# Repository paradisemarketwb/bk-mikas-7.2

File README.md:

# БК Микас7.2 · HUNTER R2

> **Hunter Reference preview:** ветка `feat/hunter-reference-ui`,
> [PR №3](https://github.com/paradisemarketwb/bk-mikas-7.2/pull/3).
> Classic R2 сохранён; новый стиль, жесты, конструктор и калибровки описаны
> в [статусе Hunter](docs/lvgl/HUNTER_STATUS.md). В main до приёмки не сливается.

Круглый сенсорный бортовой компьютер для УАЗ Hunter / ЗМЗ-409 / Микас7.2:
Waveshare ESP32-S3-Touch-LCD-2.1,480×480, проводная K-Line через L9637D.
Работает без интернета; телефон подключается к локальной сети прибора.

Это действующая переработанная версия проекта. Старые R0/R1/R1B, инструкции,
рисунки и браузерное демо находятся только в [archive/r1b](archive/README.md).

**Разработаны** собственные схемы и PCB интерфейса и питания, Gerber/Excellon/BOM,
корпуса CAD/STL, прошивка ESP-IDF, декларативный LVGL-интерфейс, native simulator,
конструктор с телефона, NVS-профили, журналы и OTA. **Физические испытания не
проводились**: перед установкой нужны квалификация питания/импульсов, проверка
ROM/BOOT/UART, нагрева, дисплея/сенсора и посадки конкретного экземпляра.
[Точный статус по ТЗ и результаты проверок](docs/R2_STATUS.md).

## С чего начать

1. [Пошаговое начало работы](docs/GETTING_STARTED.md).
2. [Компоненты и покупка](docs/BOM.md), [заказ PCB](docs/assembly/PCB_ORDER.md).
3. [Сборка, пайка, мультиметр и стенд](docs/assembly/ASSEMBLY.md).
4. [Полная проводка и распиновка](docs/WIRING.md).
5. [Windows10: сборка и прошивка](docs/firmware/R2.md).
6. [Телефон: конструктор, JSON и OTA](docs/getting-started/PHONE.md).
7. [LVGL Simulator для Windows/Linux](simulator/README.md).
8. [Диагностика неисправностей](docs/troubleshooting/DIAGNOSTICS.md).

## Два варианта подключения

- **R2 UART/L9637D** — собственные интерфейсная и силовая платы.
- **USB-KKL / FT232RL** — дополнительная отдельная прошивка, существующий KKL,
  готовый USB-A разъём, два22Ω и внешнее5V питание. Компьютер в работе не нужен.
  [Готовая прошивка с инструкциями](downloads/README.md),
  [подключение](docs/wiring/USB_KKL.md) и [сборка/прошивка](docs/firmware/USB_KKL.md).

Режимы взаимоисключающие: GPIO19 используется либо как TX_ARM, либо как D−.
На оригинальном дисплее два USB-C, ручного USB-select нет; UART выбирается
автоматически. Для работы UART питание подаётся на J9.2, UART-портJ2 должен
быть отключён от ПК. Точные исправленные инструкции — в документации проводки.

[Как менять экраны: JSON/телефон или C-код](docs/lvgl/SCREEN_CUSTOMIZATION.md).

## Платы и корпуса

Готовые архивы: [Gerber/сверловка/BOM двух плат](hardware/fabrication/BK-R2-prototype-fabrication.zip) · [STL и исходники корпусов](hardware/fabrication/BK-R2-printable-cases.zip).

- [BK-KLINE-R2](hardware/kicad/r2/README.md): L9637D, уровни3V3,
  аппаратный TX_ARM, сервисное отключение, внешний clamp K-Line.
  [KiCad](hardware/kicad/r2/BK-KLINE-R2.kicad_pro),
  [Gerber/сверловка](hardware/kicad/r2/fabrication-prototype/),
  [BOM](hardware/kicad/r2/BOM.csv), [CAD-экспорты](hardware/kicad/r2/exports/).
- [BK-POWER-R2](hardware/kicad/power-r2/README.md): автомобильный вход,
  reverse/OV/UV, MOSFET/TVS, RECOM5V и ideal-diode ORing USB.
  [KiCad](hardware/kicad/power-r2/BK-POWER-R2.kicad_pro).
- [Корпуса R2, исходники, размеры и STL](hardware/case/r2/README.md).

Номера наших JST не повторяют12PIN Waveshare. GPIO0 исключён; GPIO19 занят
TX_ARM, nativeUSB запрещён в UART-режимеR2. Рабочее питание — J9.2 USB_5V; обаType-C пустые. Для прошивки снятьJP1 и временно подключитьПК к отдельному UART Type-C J2/CH343. РучногоUSB-select нет; наличиеVBUS наJ2 автоматически отключает внешнийUART43/44. После прошивки снятькабель. Прямые12В на дисплей запрещены. Дополнительный режим [USB-KKL без R2-плат](docs/wiring/USB_KKL.md) используетGPIO19/20 какUSB; R2-жгут при этом отключается.
Файлы производства получены из реальных PCB, но программные ERC/DRC не являются
испытанием load dump или серийной автомобильной квалификацией.

## Прошивка и интерфейс

ESP-IDF5.5.1 + LVGL9.6.0. Собственный monitor0B,9600,8N1 из
[uaz-mikas-diagnostics](https://github.com/paradisemarketwb/uaz-mikas-diagnostics).
Реализованы framing/checksum/escaping/echo, reconnect и чтение11метрик/DTC.
Команд записи EEPROM, управления форсунками/вентилятором и стирания ошибок нет.

До8приборов по8виджетов: числа, подписи, дуги, стрелка, уровень, температура,
статус, предупреждение и мини-график. JSON задаёт положение/размер, метрику,
диапазон/пороги, цвет/фон, единицы, точность и видимость. Добавление экрана
не требует менять протокол ЭБУ. Есть10базовых видов, темы, свайпы, сенсорный
редактор, яркостьPWM, векторная заставкаHunter и подробные ошибки.
[Общий код и API](docs/lvgl/IMPLEMENTATION.md).

Телефон: WPA2 с уникальным паролем + отдельная HTTP-авторизация, просмотр
данных/ошибок/истории, конструктор, порядок/тема/яркость, JSON import/export,
заводской профиль и OTA в неактивный раздел с проверкой SHA256/ESP-образа.
[Исходник страницы](firmware/components/wifi/index.html),
[вид на телефоне](docs/images/web/phone-editor.png).

Скорость, пробег, остаток топлива и запас хода без датчиков не выдумываются.
ДМРВ ждёт подтверждения коэффициента, лямбда отображается raw. Данные
скриншотов и симулятора искусственные. Референс-изображения десяти экранов
в текущих вложениях нет, соответствие ему не заявляется.

## Проверки и документация

- [Архитектура](docs/ARCHITECTURE.md) и [протокол/формулы](docs/PROTOCOL.md).
- [Команды проверок и отчёты](docs/TESTING.md).
- [Сверка всех пунктов ТЗ](docs/requirements/MATRIX.md), [исходное ТЗ](docs/requirements/SPEC.md).
- [GitHub PR](https://github.com/paradisemarketwb/bk-mikas-7.2/pull/1).

Публичный репозиторий не содержит персональных диагностических логов, VIN,
паролей владельца и ключей. Уникальные credentials генерируются только на устройстве.

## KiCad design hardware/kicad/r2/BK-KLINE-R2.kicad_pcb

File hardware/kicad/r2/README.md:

# BK-KLINE-R2 — интерфейс Микас7.2

Настоящая схема и двухслойная PCB65×52mm,49 подключённых площадок. GPIO0 исключён, предусмотрены L9637D, аппаратный буферTX,22Ω pulse-proof ветвь и SMAJ18A clamp. ERC/DRC/netlist проверены программно. **Стендовых и автомобильных испытаний не было.**

- [Схема](BK-KLINE-R2.kicad_sch), [PCB](BK-KLINE-R2.kicad_pcb), [проект](BK-KLINE-R2.kicad_pro), [BOM](BOM.csv), [соединения](NETLIST.csv).
- [PDF схемы](exports/BK-KLINE-R2.pdf), [SVG схемы](exports/BK-KLINE-R2.svg), [верх](exports/pcb-top.svg), [низ](exports/pcb-bottom.svg), [3D](exports/pcb-3d.png), [STEP](exports/BK-KLINE-R2.step).
- [Gerber/позиции/PTH/NPTH](fabrication-prototype/), [ERC](reports/ERC.txt), [DRC](reports/DRC.txt), [SHA256](reports/SHA256.json).

## Подключение

|Разъём|Назначение|
|---|---|
|J1.1|VS_PROT от защищённой POWERJ2.1; не сыройACC|
|J1.2|GND от POWERJ2.2|
|J1.3|Ответвление K-Line, ориентир контакт11 колодкиУАЗ, подтвердить автомобиль|
|J3.1/J3.2|5V_OUT/GND от POWERJ2.3/J2.4|
|J2.1|5V дисплея|
|J2.2|GND дисплея|
|J2.3|3V3 **от** дисплея, питание логики интерфейса|
|J2.4|ESP_TX=GPIO43/TXD Waveshare|
|J2.5|ESP_RX=GPIO44/RXD Waveshare|
|J2.6|TX_ARM=GPIO19/D− Waveshare, nativeUSB запрещён|

J2 — **собственныйJST-XH6pin**, не последовательность12PIN Waveshare. Подключать по именам сигналов и схеме конкретной ревизии дисплея. Полная силовая схема и USB-interposer: [BK-POWER-R2](../power-r2/README.md), [жгут](../../../docs/WIRING.md). Одна общая масса. Штатный провод K-Line не разрезается, устройство подключается ответвлением; JP1 отключает только нашу ветвь.

## Безопасное включение TX

R4=100k удерживает затвор2N7002 низким; R3=10k держит `/OE` U2 высоким. HIGH на GPIO19 открывает Q1 и разрешает TX. При отключении буфера R6 подтягивает L9637.TX к3V3. GPIO0/BOOT не соединён с интерфейсом. L9637.VCC=3.3V допустимо по [ST datasheet table5](https://www.st.com/resource/en/datasheet/l9637.pdf), диапазон3–7V.

В UART-режимеR2 nativeUSB используетGPIO19, поэтому запрещён. Рабочее питание дисплея: **WaveshareJ9.2 USB_5V**; обаType-C свободны. Для прошивки разомкнутьJP1 и временно подключитьПК к отдельному UARTType-CJ2/CH343. РучногоUSB-select нет: U10 автоматически изолирует внешнийUART43/44 при появленииVBUS наJ2. После прошивки **полностью вынуть кабель**. Не питатьUARTJ2 от постоянного5V_OUT; это отключает диагностическийUART. ARM разрешается программой после конфигурации UART; поведениеROM/BOOT/RESET/brownout необходимо подтвердить осциллографом на своей ревизии Waveshare. Аппаратная схема не выдаётся за пройденную проверку ROM.

## Защита K-Line

JP1→R7=22Ω→L9637.K; SMAJ18A между K_CHIP иGND, катод кK_CHIP.18V standoff выше штатных14.7V, clamp около29.2V ниже абсолютного40V K-пина; отрицательный импульс ограничивается прямым диодом TVS. R7 — конкретный CRCW120622R0FKEAHP, pulse-proof1206,0.75W при70°C; маркировка схемы `pulse1W` не означает1W непрерывно при любой температуре. Для примера100V/50Ω/50µs: I≈(100−29.2)/(50+22)=0.98A, R7~21.3W, E~1.07mJ. Соответствие искажений/импульсной кривой/внешних форм EMC проверить отдельно. Это не сертификация ISO или доказательство отсутствия bus-loading. При отказе TVS/драйвера JP1 отключает ветвь и возвращает штатную диагностику.

## Изготовление

FR-4,1.6mm,2 слоя35µm, clearance0.25mm, минимальное сверление0.25mm. Все footprints соответствуют указанным корпусам, временных автомобильных разъёмов-заглушек нет: Phoenix/JST предназначены для монтажа внутри корпуса с фиксацией жгута. GND-via уU2 вынесен из площадки; обязательного заполнения via-in-pad не требуется. НулевойDRC подтверждает геометрию правил, но не автомобильную квалификацию. Механические и температурные допуски проверить при сборке.

Проверка обеих плат: `/usr/bin/python3 tools/check_r2_hardware.py`; экспорт из настоящегоPCB: `python3 tools/hardware/export_kicad.py --board r2`. Выбранные [3D модели](../models3d/README.md) включены в STEP, не являются измерением реальных деталей.

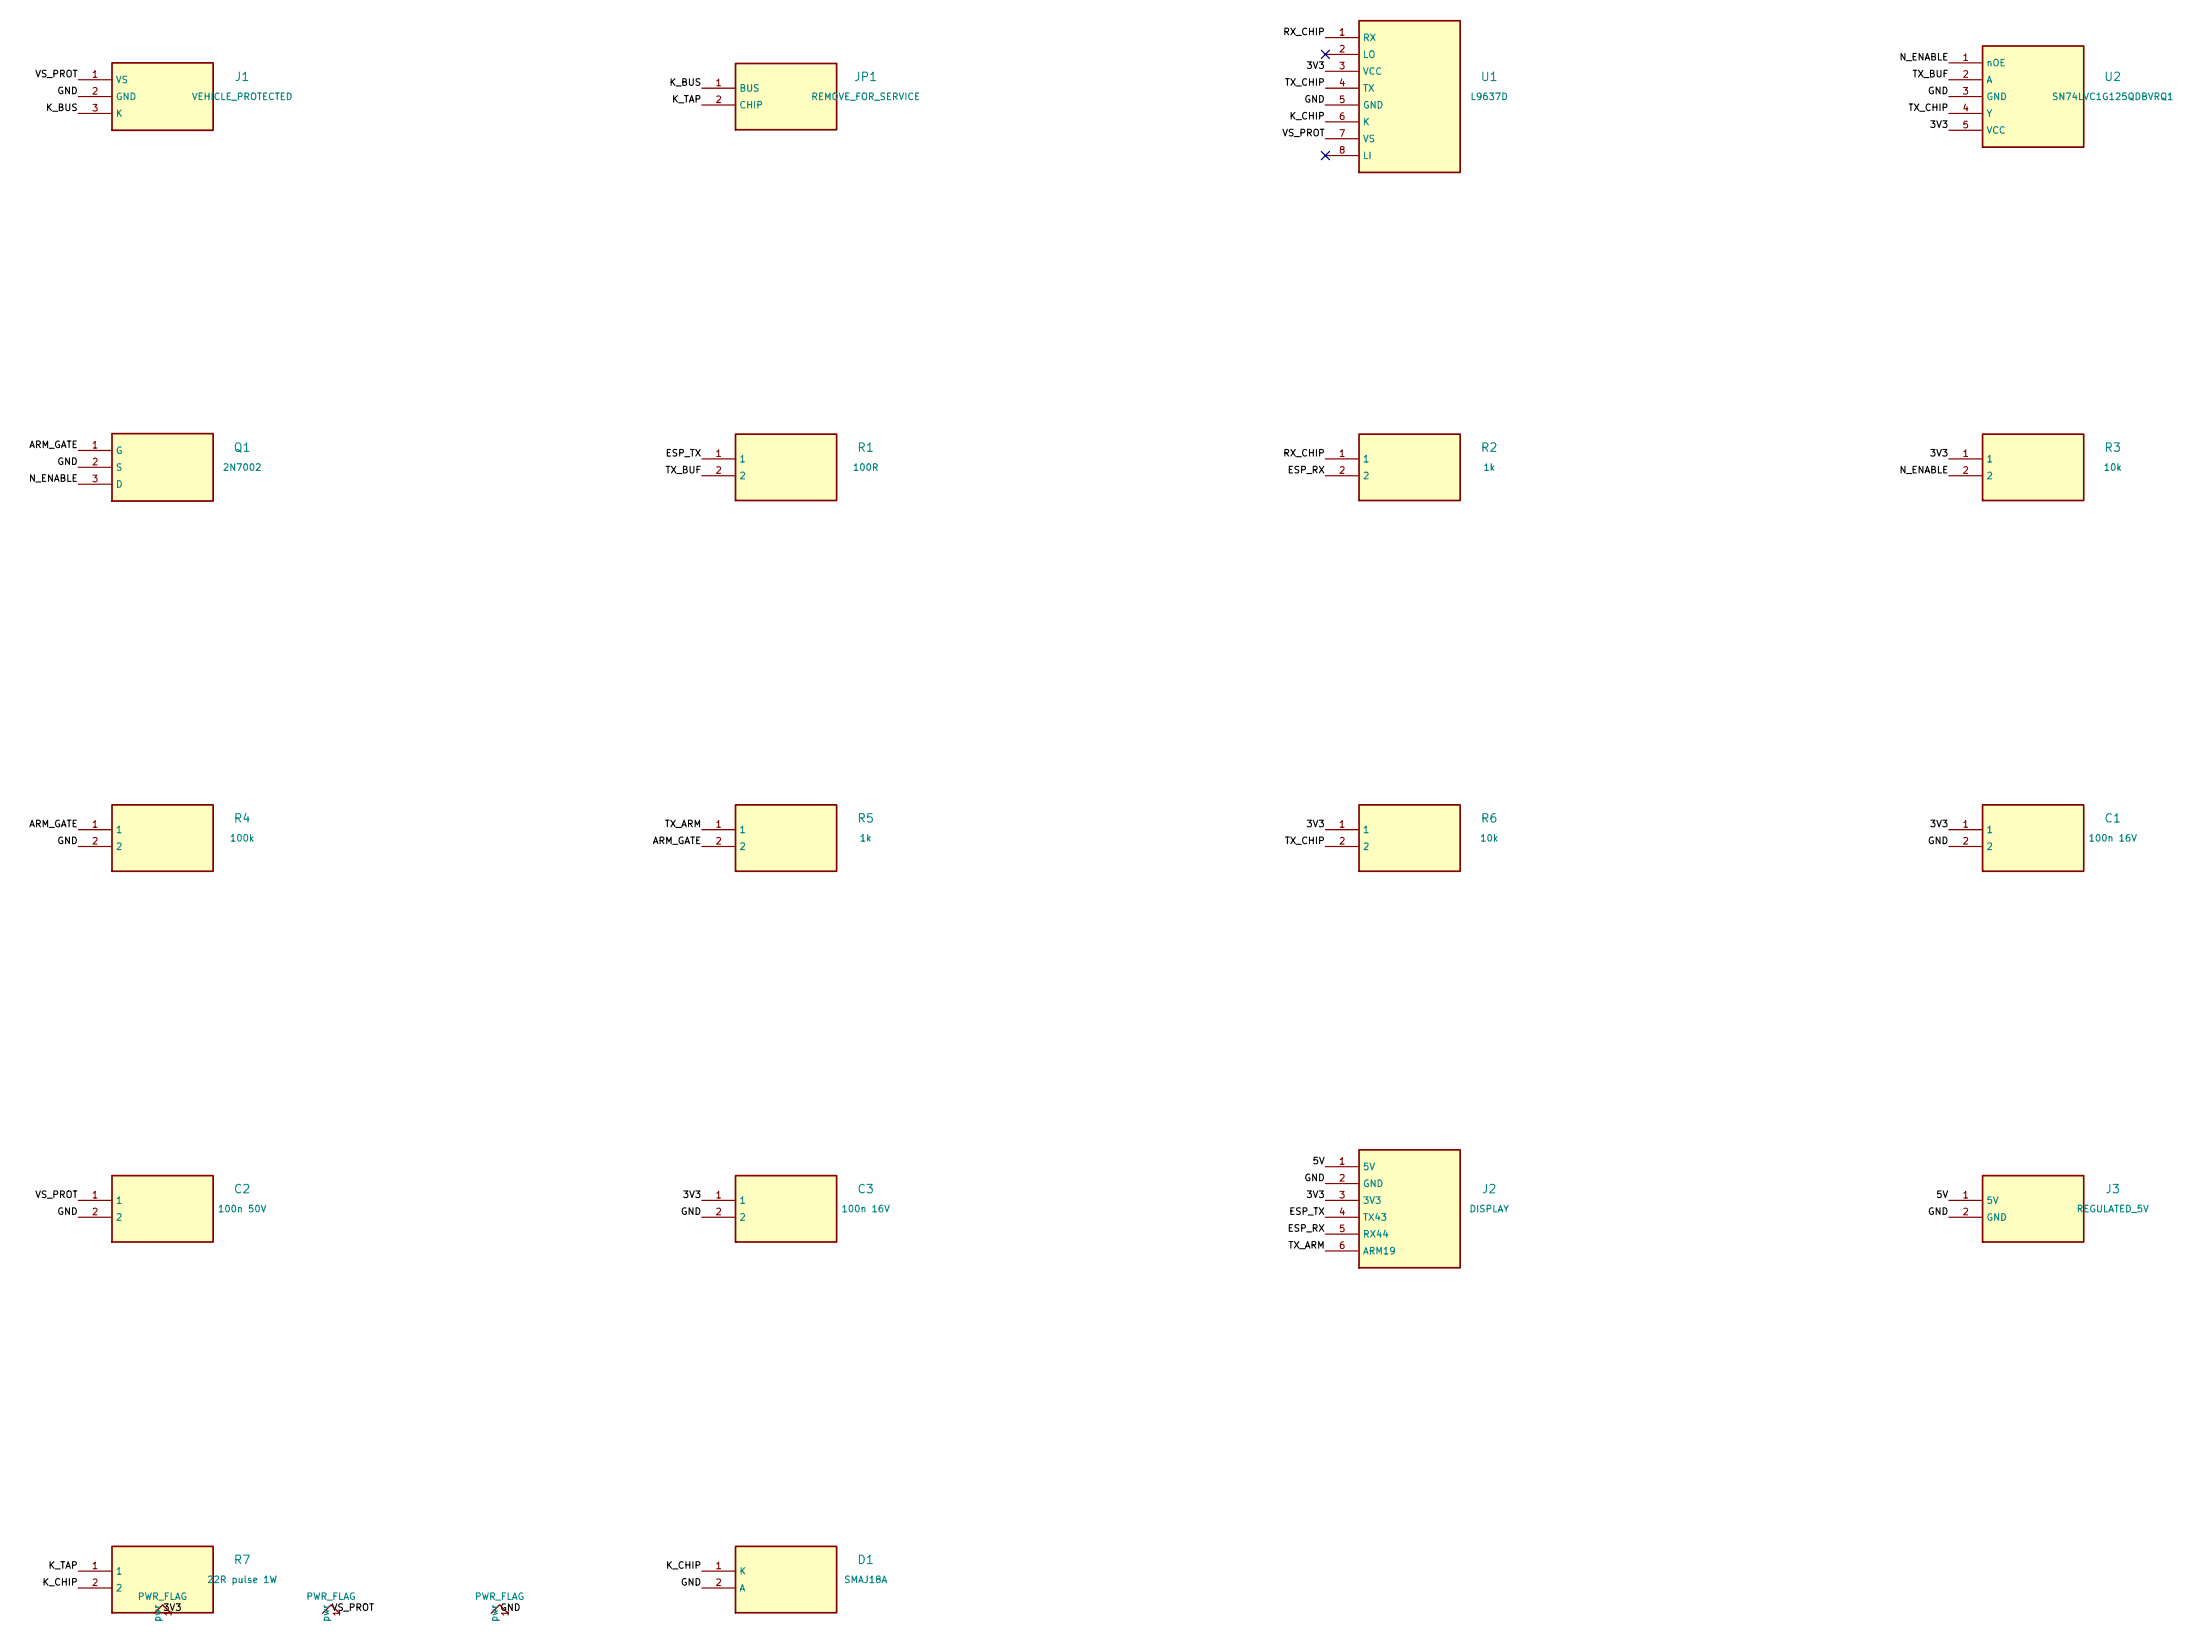
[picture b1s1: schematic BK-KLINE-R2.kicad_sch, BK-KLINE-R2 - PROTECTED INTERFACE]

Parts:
C1, C3: 100n 16V; C_0805_2012Metric
C2: 100n 50V; C_0805_2012Metric
D1: SMAJ18A; D_SMA
J1: VEHICLE_PROTECTED; TerminalBlock_Phoenix_MKDS-1,5-3-5.08_1x03_P5.08mm_Horizont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
J2: DISPLAY; JST_XH_B6B-XH-A_1x06_P2.50mm_Vertical
J3: REGULATED_5V; TerminalBlock_Phoenix_MKDS-1,5-2-5.08_1x02_P5.08mm_Horizont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
JP1: REMOVE_FOR_SERVICE; PinHeader_1x02_P2.54mm_Vertical
Q1: 2N7002; SOT-23
R1: 100R; R_0805_2012Metric
R2, R5: 1k; R_0805_2012Metric
R3, R6: 10k; R_0805_2012Metric
R4: 100k; R_0805_2012Metric
R7: 22R pulse 1W; R_1206_3216Metric
U1: L9637D; SOIC-8_3.9x4.9mm_P1.27mm
U2: SN74LVC1G125QDBVRQ1; SOT-23-5

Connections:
/3V3: C1.1, C3.1, J2.3 (3V3), R3.1, R6.1, U1.3 (VCC), U2.5 (VCC)
/5V: J2.1 (5V), J3.1 (5V)
/ARM_GATE: Q1.1 (G), R4.1, R5.2
/ESP_RX: J2.5 (RX44), R2.2
/ESP_TX: J2.4 (TX43), R1.1
/GND: C1.2, C2.2, C3.2, D1.2 (A), J1.2 (GND), J2.2 (GND), J3.2 (GND), Q1.2 (S), R4.2, U1.5 (GND), U2.3 (GND)
/K_BUS: J1.3 (K), JP1.1 (BUS)
/K_CHIP: D1.1 (K), R7.2, U1.6 (K)
/K_TAP: JP1.2 (CHIP), R7.1
/N_ENABLE: Q1.3 (D), R3.2, U2.1 (nOE)
/RX_CHIP: R2.1, U1.1 (RX)
/TX_ARM: J2.6 (ARM19), R5.1
/TX_BUF: R1.2, U2.2 (A)
/TX_CHIP: R6.2, U1.4 (TX), U2.4 (Y)
/VS_PROT: C2.1, J1.1 (VS), U1.7 (VS)

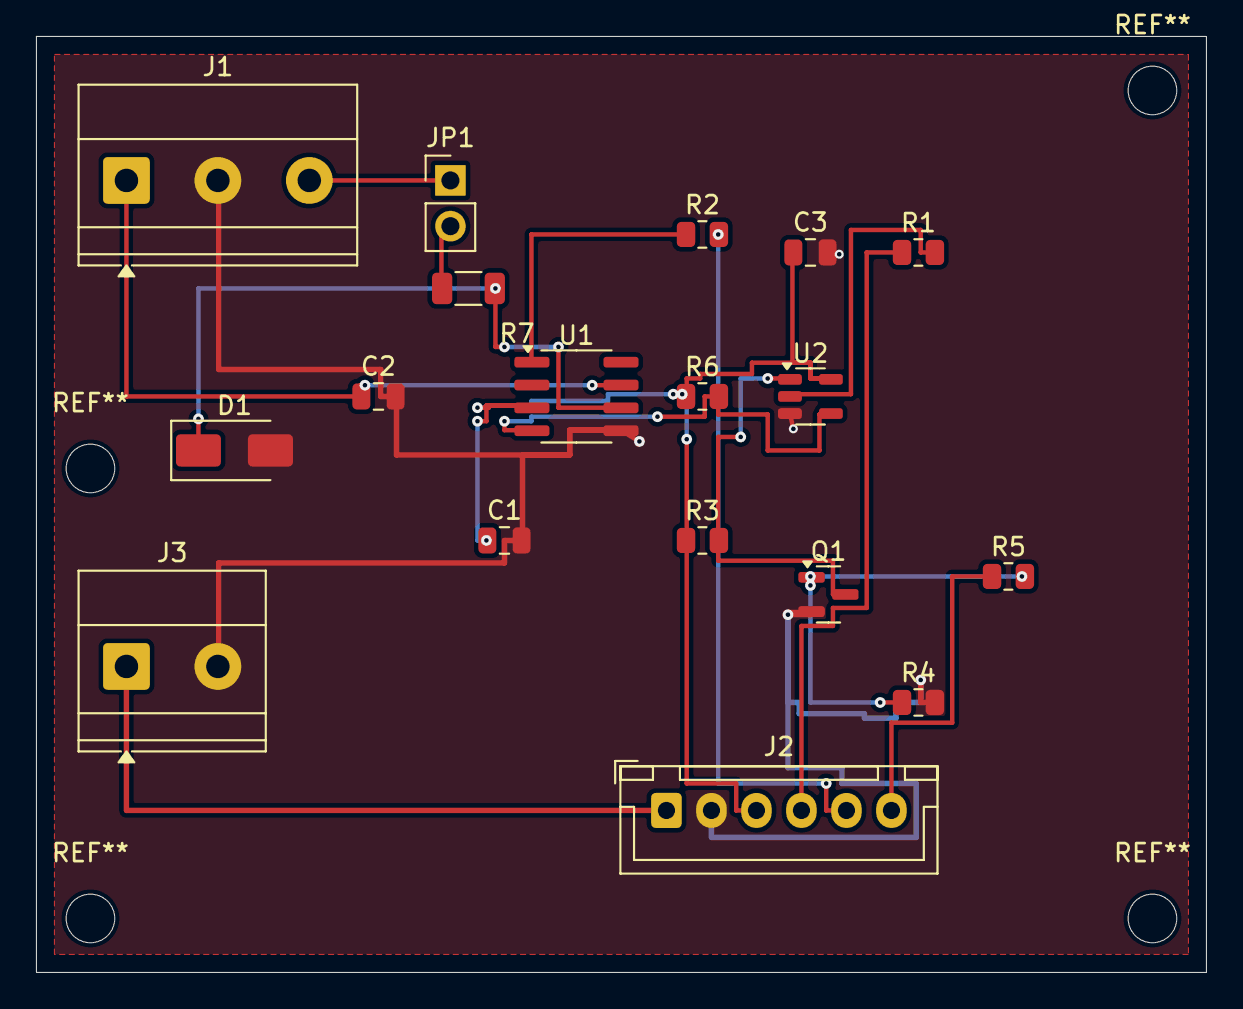
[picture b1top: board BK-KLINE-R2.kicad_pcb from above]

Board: 2 copper layers, 65.0 x 52.0 mm, 18 parts (0 on the bottom side), 15 nets.

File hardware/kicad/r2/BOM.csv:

Reference,Value,Footprint,Manufacturer_PN
C1,100n 16V,Capacitor_SMD:C_0805_2012Metric,GRM21BR71H104KA01L (100nF X7R 50V 0805)
C2,100n 50V,Capacitor_SMD:C_0805_2012Metric,GRM21BR71H104KA01L (100nF X7R 50V 0805)
C3,100n 16V,Capacitor_SMD:C_0805_2012Metric,GRM21BR71H104KA01L (100nF X7R 50V 0805)
D1,SMAJ18A,Diode_SMD:D_SMA,SMAJ18A-TR
J1,VEHICLE_PROTECTED,"TerminalBlock_Phoenix:TerminalBlock_Phoenix_MKDS-1,5-3-5.08_1x03_P5.08mm_Horizontal","Phoenix Contact MKDS 1,5/3-5,08"
J2,DISPLAY,Connector_JST:JST_XH_B6B-XH-A_1x06_P2.50mm_Vertical,JST B6B-XH-A(LF)(SN); mating XHP-6 + SXH-001T-P0.6
J3,REGULATED_5V,"TerminalBlock_Phoenix:TerminalBlock_Phoenix_MKDS-1,5-2-5.08_1x02_P5.08mm_Horizontal","Phoenix Contact MKDS 1,5/2-5,08"
JP1,REMOVE_FOR_SERVICE,Connector_PinHeader_2.54mm:PinHeader_1x02_P2.54mm_Vertical,2.54mm 1x02 pin header + removable shunt; service disconnect only
Q1,2N7002,Package_TO_SOT_SMD:SOT-23,"Nexperia 2N7002,215 (SOT-23 G=1 S=2 D=3)"
R1,100R,Resistor_SMD:R_0805_2012Metric,RC0805FR-07100RL
R2,1k,Resistor_SMD:R_0805_2012Metric,RC0805FR-071KL
R3,10k,Resistor_SMD:R_0805_2012Metric,RC0805FR-0710KL
R4,100k,Resistor_SMD:R_0805_2012Metric,RC0805FR-07100KL
R5,1k,Resistor_SMD:R_0805_2012Metric,RC0805FR-071KL
R6,10k,Resistor_SMD:R_0805_2012Metric,RC0805FR-0710KL
R7,22R pulse 1W,Resistor_SMD:R_1206_3216Metric,CRCW120622R0FKEAHP
U1,L9637D,Package_SO:SOIC-8_3.9x4.9mm_P1.27mm,L9637D
U2,SN74LVC1G125QDBVRQ1,Package_TO_SOT_SMD:SOT-23-5,SN74LVC1G125QDBVRQ1

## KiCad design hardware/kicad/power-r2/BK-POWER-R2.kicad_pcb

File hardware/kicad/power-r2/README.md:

# BK-POWER-R2 — защищённое питание и USB-интерпозер

Реальные KiCad схема/двухслойная PCB90×70mm, BOM, Gerber и разделённое сверлениеPTH/NPTH. ERC/DRC и netlist проверены программно; физической автомобильной квалификации не было. **Перед монтажом в автомобиль выполнить проверки из [расчёта](CALCULATIONS.md).**

ACC → внешний2A предохранитель → LM74800/common-source Q1/Q2 с отсечкой перенапряжения/переполюсовки → VS_PROT → RECOMR-78B5.0-2.0 → автоLM66100. ВходUSB_HOST_VBUS проходит через второйLM66100. Общая сеть **5V_OR** поступает на **TPS2553DBVR**,22.1k ILIM, и только после него получается **5V_OUT**. Проектный непрерывный ток1.0A; худший расчётный порог ограничения~1.26A, ниже1.5A LM66100.2A в маркировке RECOM не является токовым допуском всего БК.

## Файлы и проверка

- [Схема](BK-POWER-R2.kicad_sch), [PCB](BK-POWER-R2.kicad_pcb), [проект](BK-POWER-R2.kicad_pro), [локальный WSON footprint](BK_POWER.pretty/WSON-12_DRR_3x3_EP1.3x2.5.kicad_mod).
- [СхемаPDF](exports/BK-POWER-R2.pdf), [SVG](exports/BK-POWER-R2.svg), [верхPCB](exports/pcb-top.svg), [низPCB](exports/pcb-bottom.svg), [3D](exports/pcb-3d.png), [STEP](exports/BK-POWER-R2.step).
- [BOM с MPN](BOM.csv), [позиционирование](fabrication-prototype/positions.csv), [Gerber/Excellon](fabrication-prototype/).
- [ERC](reports/ERC.txt), [DRC](reports/DRC.txt), [экспортированныйnetlist](reports/netlist.xml), [SHA256](reports/SHA256.json).

STEP включает доступные модели стандартных корпусов KiCad; у собственного WSON пока нет объёмной модели. Поэтому STEP нельзя использовать как доказательство всей компонентной геометрии. Все использованные модели/лицензия/источники находятся в [models3d](../models3d/README.md), временных внешних путей для готового STEP нет.

## Разъёмы — вид на маркировку pin1 PCB

|Разъём|Pin|Цепь/подключение|
|---|---:|---|
|J1 Phoenix2pin|1|ACC_RAW, только после внешнего предохранителя2A у точки зажигания|
|J1|2|Общая масса автомобиля|
|J2 JST-XH4pin|1|VS_PROT после MOSFET-защиты, **доDC/DC** → KLINEJ1.1|
|J2|2|GND → KLINEJ1.2|
|J2|3|5V_OUT после ORing/TPS2553 → KLINEJ3.1 → WaveshareJ9.2 USB_5V|
|J2|4|GND → KLINEJ3.2|
|J3 JST-XH2pin|1|USB_HOST_VBUS, дополнительный вход внешних5V; не постоянный пигтейл вUARTпорту|
|J3|2|USB GND|

K-Line не подключается к силовой плате, она идёт ответвлением на KLINEJ1.3. Постоянное питание диагностической колодки по умолчанию не используется. [Полный жгут](../../../docs/WIRING.md).

## USB и автоматический UART Waveshare

У оригинального2.1 **два**USB-C: WaveshareJ2 USB TO UART/CH343 и J3 nativeUSB19/20. РучногоUSB-select нет. U10FSUSB42 выбирает CH343 по наличиюJ2.VBUS и при этом отключает внешнийUART43/44. Поэтому в рабочемR2 режиме дисплей питается от5V_OUT **только черезJ9.2 USB_5V**, обаType-C пустые.

POWERJ3 — необязательный дополнительный вход5V черезLM66100. Предыдущее указание разрезатьVBUS USB-кабеля и подать `POWER5V_OUT→WaveshareUARTJ2.VBUS` **ошибочно и отменено**: такое питание постоянно переключаетU10 и лишает БК внешнегоUART. ФизическиеPCBPOWER/KLINE от этого не меняются; исправляется жгут.

Для прошивки снятьJP1 и временно подключитьПК обычнымкабелем к **UARTType-CJ2**, затем полностьюотключитькабель до возвратаJP1. D1/D8 в официальной схемеWaveshare пропускают UARTJ2.VBUS вVCC/USB_5V и блокируют обратный ток; проверять свою ревизию на стенде. Прямое сервисное питание дисплея черезJ2 не проходит нашTPS2553, поэтому не является штатным автомобильным режимом.

**NativeType-CJ3.VBUS иJ9.2 — одна сеть.** ПК кnativeJ3 при внешнемпитании не подключать: это может обойти развязку; вUARTрежиме егоD− дополнительно занятARM19. ДваLM66100 защищают свои входы, а не любое произвольное подключениеPC к дисплею. Идеальные диоды не обеспечивают гальваническую развязку земли. БюджетUSB2/USB3 и согласование нагрузки хостом сохраняются.

[Подробности и первичная схема](../../../docs/WIRING.md). [Отдельный USB-KKL Host без нашихPCB](../../../docs/wiring/USB_KKL.md) требует отключить R2-жгут и подать отдельные5V на дисплей/KKL; nativeUSBGPIO19/20 тогда используются толькоUSBHost.

## Сборка и изготовление

FR-4,1.6mm,2 слоя35µm Cu, signal width/clearance0.15mm, RAW clearance0.8mm, сверление0.25mm и выше. Фабрике передаются7 Gerber, **обаPTH/NPTH Excellon**, BOM и позиционирование при заказе монтажа. См. текущий архив [производственных пакетов](../../fabrication/), который собирается из этих экспортов. Нужна оптическая проверка и контроль схемы перед заказом серии; это инженерная ревизия.

LM74800: pin1 отмечен точкой/цифрой на шелкографии и ключом наF.Fab. **RTN/pad13 паять на собственную изолированную площадку, не соединять сGND.** Проверить ориентациюQ1/Q2, полосы катодовD1/D2/D3/D5/D6; D4 двунаправленный. Не подменять силовые CRCW-HP обычными0805. Номиналы и полные MPN — вBOM. Компоненты generic standard grade не объявляются AEC-Q-квалифицированными; предел температуры/вибрации проверяется для сборки в целом.

Воспроизведение: `python3 tools/hardware/export_kicad.py --board power-r2` из корня, затем `/usr/bin/python3 tools/check_r2_hardware.py`. Для генерации схемы: `/usr/bin/python3 tools/hardware/generate_power_r2.py`; опция `--initial-pcb` создаёт только исходную расстановку и **не заменяет финальную трассировку**.

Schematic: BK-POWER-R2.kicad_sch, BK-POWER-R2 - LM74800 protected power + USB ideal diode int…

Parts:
C1: 100n 630V X7R; C_1210_3225Metric
C2: 4u7 100V X7S; C_1210_3225Metric
C3, C7, C9, C10: 100n 50V X7R; C_0805_2012Metric
C4: 1u 50V; C_0805_2012Metric
C5: 10u 50V X7R; C_1210_3225Metric
C6, C8: 10u 16V X7R; C_1206_3216Metric
D1: BZG03B62-M / 62V; D_SMA
D2: BAS21H,115; D_SOD-123F
D3: SMBJ150A; D_SMB
D4: SMBJ33CA; D_SMB
D5: SMBJ18A; D_SMB
D6: SS110 / negative VS clamp; D_SMA
J1: ACC_IN_FUSED_2A; TerminalBlock_Phoenix_MKDS-1,5-2-5.08_1x02_P5.08mm_Horizont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
J2: VS_AND_5V_OUT; JST_XH_B4B-XH-A_1x04_P2.50mm_Vertical
J3: USB_HOST_5V_GND; JST_XH_B2B-XH-A_1x02_P2.50mm_Vertical
Q1: IPD50R380CE; TO-252-2
Q2: BUK7Y4R8-60E; LFPAK56
R1: 10k 1W 400V pulse; R_2010_5025Metric
R2, R4: 100k 0.75W 200V; R_1206_3216Metric
R3: 7k5 1%; R_0805_2012Metric
R5: 18k 1%; R_0805_2012Metric
R6: 22k1 1%; R_0805_2012Metric
TP1: ACC_RAW; TestPoint_Pad_D1.5mm
TP2: VS_PROT; TestPoint_Pad_D1.5mm
TP3: 5V_CAR; TestPoint_Pad_D1.5mm
TP4: 5V_OUT; TestPoint_Pad_D1.5mm
TP5: GND; TestPoint_Pad_D1.5mm
U1: LM74800QDRRRQ1; WSON-12_DRR_3x3_EP1.3x2.5
U2: R-78B5.0-2.0; Converter_DCDC_RECOM_R-78B-2.0_THT
U3, U4: LM66100DCKR; SOT-363_SC-70-6
U5: TPS2553DBVR / current limit; SOT-23-6

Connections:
/5V_CAR: C6.1, C7.1, TP3.1, U2.3 (5V), U3.1 (VIN)
/5V_OR: C10.1, U3.3 (nCE), U3.6 (VOUT), U4.3 (nCE), U4.6 (VOUT), U5.1 (IN), U5.3 (EN)
/5V_OUT: C8.1, J2.3 (5V_OUT), TP4.1, U5.6 (OUT)
/ACC_RAW: C1.1, D3.1, J1.1 (ACC), Q1.2 (D), R1.1, R2.1, R4.1, TP1.1
/CAP: C3.2, U1.11 (CAP)
/COMMON_SOURCE: C4.1, D2.2, Q1.3 (S), Q2.1 (S), Q2.2 (S), Q2.3 (S), U1.2 (A), U1.9 (OUT)
/CTRL_VS: C2.1, C3.1, D1.1, D2.1, D6.1 (K), R1.2, U1.3 (VSNS), U1.4 (SW), U1.10 (VS)
/DGATE: Q2.4 (G), U1.1 (DGATE)
/GND: C1.2, C2.2, C4.2, C5.2, C6.2, C7.2, C8.2, C9.2, C10.2, D1.2, D4.1, D5.2, D6.2 (A), J1.2 (GND), J2.2 (GND), J2.4 (GND), J3.2 (GND), R3.2, R5.2, R6.2, TP5.1, U1.7 (GND), U2.2 (GND), U3.2 (GND), U4.2 (GND), U5.2 (GND)
/HGATE: Q1.1 (G), U1.8 (HGATE)
/ILIM: R6.1, U5.5 (ILIM)
/OV_SENSE: R2.2, R3.1, U1.5 (OV)
/TVS_MID: D3.2, D4.2
/USB_5V: C9.1, J3.1 (VBUS), U4.1 (VIN)
/UV_SENSE: R4.2, R5.1, U1.6 (EN_UVLO)
/VS_PROT: C5.1, D5.1, J2.1 (VS_PROT), Q2.5 (D), TP2.1, U1.12 (C), U2.1 (VIN)

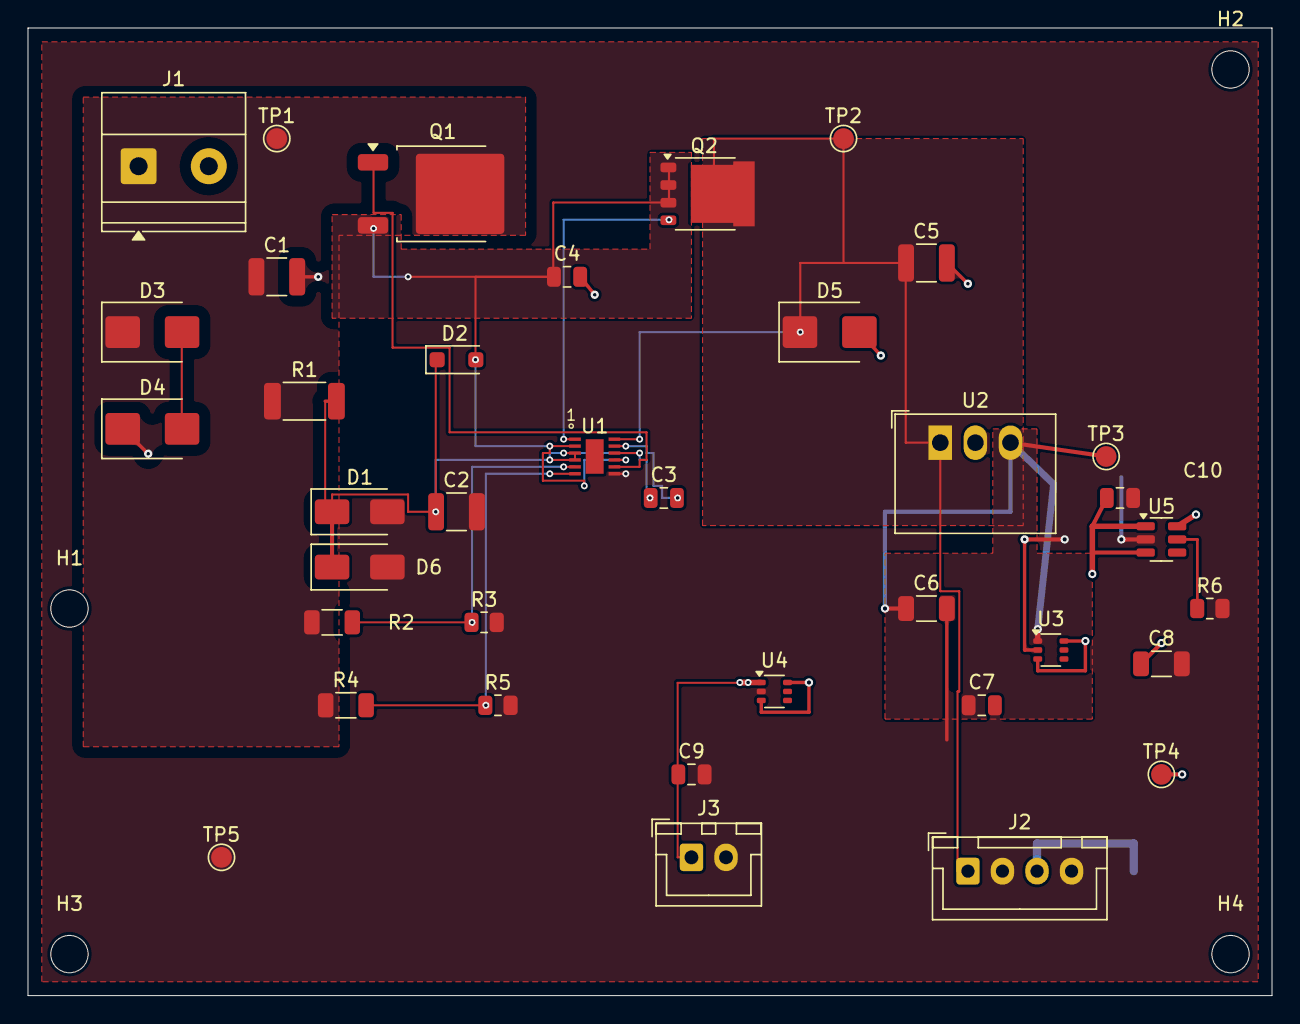
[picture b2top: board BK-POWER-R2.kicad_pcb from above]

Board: 2 copper layers, 90.0 x 70.0 mm, 41 parts (0 on the bottom side), 16 nets.

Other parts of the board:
H1, H2, H3, H4: MountingHole_2.7mm_M2.5

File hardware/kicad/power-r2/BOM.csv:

Reference,Value/MPN,Footprint
J1,ACC_IN_FUSED_2A,"TerminalBlock_Phoenix:TerminalBlock_Phoenix_MKDS-1,5-2-5.08_1x02_P5.08mm_Horizontal"
Q1,IPD50R380CE,Package_TO_SOT_SMD:TO-252-2
Q2,BUK7Y4R8-60E,Package_TO_SOT_SMD:LFPAK56
U1,LM74800QDRRRQ1,BK_POWER:WSON-12_DRR_3x3_EP1.3x2.5
R1,10k 1210 0.5W 200V,Resistor_SMD:R_1210_3225Metric
D1,BZG03C56G,Diode_SMD:D_SMA
D2,"BAS21H,115",Diode_SMD:D_SOD-123F
D3,SMBJ150A,Diode_SMD:D_SMB
D4,SMBJ33CA,Diode_SMD:D_SMB
C1,100n 250V,Capacitor_SMD:C_1210_3225Metric
C2,1u 100V X7R,Capacitor_SMD:C_1210_3225Metric
C3,100n 25V,Capacitor_SMD:C_0805_2012Metric
C4,1u 50V,Capacitor_SMD:C_0805_2012Metric
R2,100k 1% 200V,Resistor_SMD:R_1206_3216Metric
R3,7k5 1%,Resistor_SMD:R_0805_2012Metric
R4,100k 1% 200V,Resistor_SMD:R_1206_3216Metric
R5,18k 1%,Resistor_SMD:R_0805_2012Metric
D5,SMBJ18A,Diode_SMD:D_SMB
C5,10u 50V X7R,Capacitor_SMD:C_1210_3225Metric
U2,R-78B5.0-2.0,Converter_DCDC:Converter_DCDC_RECOM_R-78B-2.0_THT
C6,10u 16V X7R,Capacitor_SMD:C_1206_3216Metric
U3,LM66100DCKR,Package_TO_SOT_SMD:SOT-363_SC-70-6
C7,100n 16V,Capacitor_SMD:C_0805_2012Metric
C8,10u 16V X7R,Capacitor_SMD:C_1206_3216Metric
J2,VS_AND_5V_OUT,Connector_JST:JST_XH_B4B-XH-A_1x04_P2.50mm_Vertical
J3,USB_HOST_5V_GND,Connector_JST:JST_XH_B2B-XH-A_1x02_P2.50mm_Vertical
U4,LM66100DCKR,Package_TO_SOT_SMD:SOT-363_SC-70-6
C9,100n 16V,Capacitor_SMD:C_0805_2012Metric
TP1,ACC_RAW,TestPoint:TestPoint_Pad_D1.5mm
TP2,VS_PROT,TestPoint:TestPoint_Pad_D1.5mm
TP3,5V_CAR,TestPoint:TestPoint_Pad_D1.5mm
TP4,5V_OUT,TestPoint:TestPoint_Pad_D1.5mm
TP5,GND,TestPoint:TestPoint_Pad_D1.5mm

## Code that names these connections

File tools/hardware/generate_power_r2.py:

#!/usr/bin/python3
"""Generate editable R2 power schematic and initial PCB from exact component map.
Requires KiCad9 pcbnew. Existing routed PCB is NOT overwritten without --initial-pcb.
"""
from pathlib import Path
import uuid,json,csv,sys
import pcbnew as p
from power_parts import parts,mpns
root=Path(__file__).resolve().parents[2];out=root/'hardware/kicad/power-r2';out.mkdir(parents=True,exist_ok=True)
u=lambda:str(uuid.uuid4())
# TI DRR0012E recommended land pattern: 0.5 pitch; floating pad13 mandatory.
fp='(footprint "WSON-12_DRR_3x3_EP1.3x2.5" (version 20240108) (generator pcbnew) (layer "F.Cu") (attr smd) (fp_rect (start -1.5 -1.5) (end 1.5 1.5) (stroke (width .1) (type default)) (fill none) (layer "F.Fab")) (fp_rect (start -1.9 -1.75) (end 1.9 1.75) (stroke (width .05) (type default)) (fill none) (layer "F.CrtYd")) (fp_text reference "REF**" (at 0 -2.2) (layer "F.SilkS") (effects (font (size 1 1) (thickness .15))))'
fp+='(fp_circle (center -1.7 -2.2) (end -1.55 -2.2) (stroke (width .1) (type default)) (fill none) (layer "F.SilkS")) (fp_text user "1" (at -1.7 -3) (layer "F.SilkS") (effects (font (size .8 .8) (thickness .1))))'
for n in range(1,13):
 x=-1.425 if n<=6 else 1.425;y=(-1.25+(n-1)*.5) if n<=6 else (1.25-(n-7)*.5)
 fp+=f'(pad "{n}" smd rect (at {x} {y}) (size .85 .25) (layers "F.Cu" "F.Paste" "F.Mask"))'
fp+='(pad "13" smd rect (at 0 0) (size 1.3 2.5) (layers "F.Cu" "F.Paste" "F.Mask")))'
if not (out/'BK_POWER.pretty/WSON-12_DRR_3x3_EP1.3x2.5.kicad_mod').exists():
    (out/'BK_POWER.pretty/WSON-12_DRR_3x3_EP1.3x2.5.kicad_mod').write_text(fp)
(out/'fp-lib-table').write_text('(fp_lib_table (lib (name BK_POWER) (type KiCad) (uri ${KIPRJMOD}/BK_POWER.pretty) (options "") (descr "TI DRR0012E")))')
lib=[];instances=[];labels=[];rootuid=u();sources=[('ACC_RAW',14),('CTRL_VS',18),('COMMON_SOURCE',22),('VS_PROT',26),('5V_OR',34),('USB_5V',38),('GND',42)]
allparts=parts+[(f'#FLG{i}',net,'',[(net,net,'power_out')],0,0) for i,(net,_) in enumerate(sources)]
for idx,(ref,val,foot,pins,x,y) in enumerate(allparts):
 name=ref.replace('#','');sx=35.56+(idx%4)*195.58;sy=35.56+(idx//4)*50.8;h=max(5,len(pins)*1.27+1.27);isflag=ref.startswith('#');props=f'(property "Reference" "{ref}" (at 0 {-h-3} 0) (effects (font (size 1.27 1.27)))) (property "Value" "{val}" (at 0 {h+3} 0) (effects (font (size 1 1)))) (property "Footprint" "{foot}" (at 0 0 0) (effects (font (size 1 1)) (hide yes)))'
 pinstr=''
 for j,(pn,net,typ) in enumerate(pins):
  yy=round((len(pins)-1)*1.27-j*2.54,2);pinstr+=f'(pin {typ} line (at -12.7 {yy} 0) (length 5.08) (name "{pn}" (effects (font (size 1 1)))) (number "{j+1}" (effects (font (size 1 1)))))';px=sx-12.7;py=round(sy-yy,2)
  labels.append(f'(label "{net}" (at {px} {py} 0) (effects (font (size 1 1)) (justify right bottom)) (uuid "{u()}"))' if net else f'(no_connect (at {px} {py}) (uuid "{u()}"))')
 lib.append(f'(symbol "BK_POWER:{name}" (pin_names (offset .5)) (in_bom {"no" if isflag else "yes"}) (on_board {"no" if isflag else "yes"}) {props} (symbol "{name}_0_1" (rectangle (start -7.62 {-h}) (end 7.62 {h}) (stroke (width .254) (type default)) (fill (type background)))) (symbol "{name}_1_1" {pinstr}))')
 instances.append(f'(symbol (lib_id "BK_POWER:{name}") (at {sx} {sy} 0) (unit 1) (in_bom {"no" if isflag else "yes"}) (on_board {"no" if isflag else "yes"}) (dnp no) (uuid "{u()}") (property "Reference" "{ref}" (at {sx+12} {sy-3} 0) (effects (font (size 1.27 1.27)))) (property "Value" "{val}" (at {sx+12} {sy} 0) (effects (font (size 1 1)))) (property "Footprint" "{foot}" (at {sx} {sy} 0) (effects (font (size 1 1)) (hide yes))) (instances (project "BK-POWER-R2" (path "/{rootuid}" (reference "{ref}") (unit 1)))))')
sch=f'(kicad_sch (version 20231120) (generator "bk_power_r2") (uuid "{rootuid}") (paper "A1") (title_block (title "BK-POWER-R2 - LM74800 protected power + USB ideal diode interposer") (rev "R2") (comment 1 "Engineering design: bench/load-dump qualification required")) (lib_symbols '+''.join(lib)+') '+''.join(labels)+''.join(instances)+')'
(out/'BK-POWER-R2.kicad_sch').write_text(sch)
(out/'BK_POWER.kicad_sym').write_text('(kicad_symbol_lib (version 20231120) (generator bk_power_r2) '+''.join(lib).replace('(symbol "BK_POWER:','(symbol "')+')')
(out/'sym-lib-table').write_text('(sym_lib_table (lib (name BK_POWER) (type KiCad) (uri ${KIPRJMOD}/BK_POWER.kicad_sym) (options "") (descr "Original power symbols")))')
if not (out/'BK-POWER-R2.kicad_pro').exists():(out/'BK-POWER-R2.kicad_pro').write_text(json.dumps({'board':{'design_settings':{'rules':{'min_clearance':.15,'min_track_width':.15,'min_through_hole_diameter':.25}}}},indent=2))
with (out/'BOM.csv').open('w') as f:
 w=csv.writer(f);w.writerow(['Reference','Value','Footprint','Manufacturer_PN']);w.writerows((c[0],c[1],c[2],mpns.get(c[0],'1.5mm plated test point; no fitted part')) for c in parts)
if '--initial-pcb' not in sys.argv:sys.exit(0)
b=p.BOARD();nets={}
for net in sorted({pi[1] for c in parts for pi in c[3] if pi[1]}):ni=p.NETINFO_ITEM(b,'/'+net);b.Add(ni);nets[net]=ni
for ref,val,fp,pins,x,y in parts:
 lib,fn=fp.split(':');folder=str(out/'BK_POWER.pretty') if lib=='BK_POWER' else '/usr/share/kicad/footprints/'+lib+'.pretty';f=p.FootprintLoad(folder,fn)
 if not f:raise ValueError(fp)
 f.SetReference(ref);f.SetValue(val);f.SetPosition(p.VECTOR2I(p.FromMM(x),p.FromMM(y)));b.Add(f)
 for pad in f.Pads():
  n=pad.GetNumber()
  if n.isdigit() and 0<int(n)<=len(pins) and pins[int(n)-1][1]:pad.SetNet(nets[pins[int(n)-1][1]])
for a,c in [((0,0),(90,0)),((90,0),(90,70)),((90,70),(0,70)),((0,70),(0,0))]:
 e=p.PCB_SHAPE();e.SetShape(p.SHAPE_T_SEGMENT);e.SetStart(p.VECTOR2I(p.FromMM(a[0]),p.FromMM(a[1])));e.SetEnd(p.VECTOR2I(p.FromMM(c[0]),p.FromMM(c[1])));e.SetLayer(p.Edge_Cuts);e.SetWidth(p.FromMM(.05));b.Add(e)
for i,(x,y) in enumerate([(3,3),(87,3),(3,67),(87,67)]):
 f=p.FootprintLoad('/usr/share/kicad/footprints/MountingHole.pretty','MountingHole_2.7mm_M2.5');f.SetReference('H'+str(i+1));f.SetPosition(p.VECTOR2I(p.FromMM(x),p.FromMM(y)));b.Add(f)
p.SaveBoard(str(out/'BK-POWER-R2.kicad_pcb'),b)
